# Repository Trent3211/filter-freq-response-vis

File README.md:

# Filter Frequency Response Visualizer
GitHub repo for SDSU Senior Design Team 18, Filter Frequency Response Visualizer, or FFRV

## SYSTEM DESCRIPTION

The FFRV system  will be a test box used for measuring the frequency response of a user-provided passive filter. Once started, the system will apply a frequency sweep across an inputted filter, then measure the filter output gain and phase shift using analog computations, inputted to an Arduino Due microcontroller. Thus, this FFRV system will calculate the Bode plots for a real-world filter. The purpose of the FFRV system is to allow students, hobbyists, and other casual filter-designers a rapid way to gain insight into simple filters, such as what frequencies they pass or reject. As such, the FFRV system will be designed to be straightforward to use. It shall have a box face with only a select few clearly-labeled inputs, and output a data file of the measurements to the user computer, connected over USB to the test box. The functional components in this system will include a procured waveform generator, a PCB for distributing power and performing analog analysis on filter magnitude and phase, an Arduino Due for converting the analog values to digital and controlling the waveform generator, and a NET application which will provide the user an interface to work with the system.

## USING GITHUB

### Basic Operation: 

Git is both local version control (local) and also cloud version control (remote). Version control is logging how changes are made to documents (think google docs history) so that way changes can be managed. This is useful in code, where you may have a working solution but you want to add features to it, so "committing" that version to a history log allows you to make changes, and always have a successful solution to return to. Basically, git is a way to log changes you make files, and then upload them to the cloud (have them stored virtually, rather than locally). That's the basic operation. There is more features that will be used, but at its most basic operation its changing files and then logging those changes. 

### Install Git:

__Create Git Repo Folder__
<br>
Purely for containment sakes, you may want to create a folder for holding all your GitHub repos. This is optional. If you already have a folder, then you have no need to create a new folder. I (Trent) would suggest creating a folder titled "GitHub-Repos" in your Documents folder on your computer. You can create that folder using the following CLI commands. (To open the terminal, type "Command Prompt" in the search function on your windows machine, then click on the application)
```
cd Documents
mkdir GitHub-Repos
cd GitHub-Repos
```
__Add the repository__
<br>
Go to the desired directory (if you followed the steps in "Create Git Repo Folder", you will already be in the desired folder) and clone the repository. The comand will look like the following
```
git clone https://github.com/Trent3211/filter-freq-response-vis.git <Optional: What you'd like the document to be named>
```
Sections wrapped by \< \> will want to be replaced by what is referred to in the section. You should be able to now see a folder with the title you provided in the `<Optional: ...>` section, or it will be titled filter-freq-reponse-vis. You can view this in your file explorer, or by using the `dir` command in the Terminal (Command Prompt). To verify that the repository was properly imported, open the folder using the Windows File explorer. Check the folder for the README.md file. Its contents should match this file. 

### Creating a commit: 

To use Git, you'll link your local to the remote. As you make changes to the whatever files you're editing (NET application, INO file, KiCAD schematic, LTSpice simulation, etc.) you'll want to mark good changes. You mark these changes with a "commit". Committing works in three phases. First, you add the files you want to a new commit (using command line interface arguments, or CLI). Second, you'll "commit" these changes to your local git with a message that describes the changes that we're made from the previous commit to the current commit (there is a standardized way for creating commit messages), using the CLI. Third, you will "push" your local changes to the remote, again using the CLI. The steps and their associated CLI arguments are shown below:
<br>

__0a) Go to repository:__ `cd <local file path for github repo> `
<br>
__0b) Pull any new changes:__ `git fetch`
<br>
__1) Add Files:__ `git add <file name1> <file name2> ... <file name x> `
<br>
-> NOTE: Use `git status` to see what changes you've made to files. Those that have been edited will appear in red. After you've added them, if you run `git status` again they should appear green.
<br>
__2) Create Log Message:__ `git commit `
<br>
-> NOTE: This will open the default text editor, "Vim". Vim slightly terrifies me, so I would recommend switching your default editor to Notepad. To set it to that text editor, see "Other Helpful CLI". See notes on creating an effective commit message in the section below
<br>
__3) Push Changes:__ `git push -u origin`
<br>
-> NOTE: origin refers to the cloud repository, as it is the first instantiation of the github repo. 
<br>
<br>
_Commit Message Best Practice_
<br>
There are two parts to a commit message: the subject header and a description. A subject header should encapsulate what was changed in the commit using 50 characters or less. If there is a lot more detail necessary to encapsulate the full picture, that's what the description is used for. Best practice for the subject header is to use the imperative tense. Examples include `Test new data`, or `Rewire ground and power planes`. A subject header should be formatted such that someone reading could read it as "If applied, this commit will ...", followed by the subject header. Thus, the following examples would read "This commit will: Test new data" or "This commit will: Rewire ground and power planes". 
<br>
After writing the subject header, two lines breaks will separate the subject header from the description. The description may add more detail not included in the subject header, reasoning for why the commit was needed, include details about testing and verification steps, or detail errors that were encountered with the version in the commit that will need to be fixed in future commits. Wrap each line of the description after 72 characters, otherwise it will be hard to read using the CLI. More detail on commit messages can be found here [https://gist.github.com/robertpainsi/b632364184e70900af4ab688decf6f53]. A good commit message may look like the following (the sections preceded by # are autogenerated by Git. They can be left in, they will not be included when viewing the message in the future):
```
Rewire ground and power planes

A previous commit had the ground and power planes connected to the same 
netlist. However, there are still some serious ratnests that may 
introduce noise. An issue has been added to the GitHub to address it.
# Please enter the commit message for your changes. Lines starting
# with '#' will be ignored, and an empty message aborts the commit.
#
# On branch fake-branch
# Your branch is up to date with 'origin/fake-branch'.
#
# Changes to be committed:
#       new file:   fake-file
```

### Creating and merging a branch

As we set up issues (think spots of development in achieving our long term milestones) in GitHub and try to solve them, we'll want to create new branches to address them. Branching keeps the main tree clean as solutions develop, so that they are only added into the `main` branch when they are finished being developed and have been reviewed by other members of the team. The naming convention for a branch is the issue number, followed by an underscore, and a 1 to 3 word description of what changes the branch encapsulates/will encapsulate. For example, a good name for a branch that addresses issue 0 of team members getting to know each other would be `0_starbucks_meeting`. Be sure to always branch from the main branch, rather than form other branches. This will keep the logging and version control easier to follow. The steps for creating a branch locally and publishing to the remote are shown below:
<br>
<br>
__0a) Update to the remote:__ 
<br>
Run `git fetch` to update your local repository with changes with those made in the remote (the online repository that we all access). Now run `git status` to see how many commits above or behind you are. If you have not made any changes that haven't yet been committed, run `git pull`. You will now be up-to-date with the remote and ready to proceed. 
<br>
__0b) Set to `main` branch:__ 
<br> Run `git status` using the CLI to make sure you are on the main branch. The first line of the text output should detail which branch you are on. If you are not on the main branch, run `git checkout main`. The output in this case should now be:
```
Switched to branch 'main'
Your branch is up to date with 'origin/main'.
```
__1) Create a new local branch:__ 
<br>
To create a new branch, there are two sets of commands you can choose. The first create a new branch off of the current branch, followed by a checkout command to switch to it. First run `git branch <Branch-Name>`. You can verify the branch was properly created by running `git branch`, which will list all available branches. Next, switch to the branch by running `git checkout <Branch-Name>`. The second method for creating a new branch both creates and switches to a branch in one command. This is `git checkout -b <Branch-Name>`. Only one of these two methods may be used to create and switch to a new branch--not both.
<br>
__2) Push branch to remote:__ 
<br>
In order to set up the branch so that it is remotely tracked, run `git push -u origin <Branch-Name>`. Now, when commits are made and pushed, they will be pushed to this branch in the remote. You are now free to add/change files and create commits
<br>
__3) Pull Request:__ 
<br>
The final part in a branches lifecycle is its death, which happens by merging it into the `main` branch. A merge into the `main` branch is called a pull request. It's poorly named, but there's no changing what GitHub refers to it as so so be it. You can find the list of branches on GitHub website by clicking "\<\> Code" when in the repositor folder. Click on the "Branches" tab. When you click on this, you will see a list of branches. Click on the "Pull Request" button next to the desired branch. Add a comment providing a paragraph description of what has been changed, and add reviewers for who should review the changes before its merged into `main`. Publish once you are ready.
<br>
### Other Helpful CLI:
`git checkout <branch name>`
<br>
`git branch`
Lists all branches currently visible on the local machine. (Other branches in the remote will be accessible using a `git checkout`, but may not be visible using git branch)
`git log` 
See all commits in the repository (if you've made new commits, these should show up here. It zhould also be synced with the remote if you've run `git fetch` and `git pull`)

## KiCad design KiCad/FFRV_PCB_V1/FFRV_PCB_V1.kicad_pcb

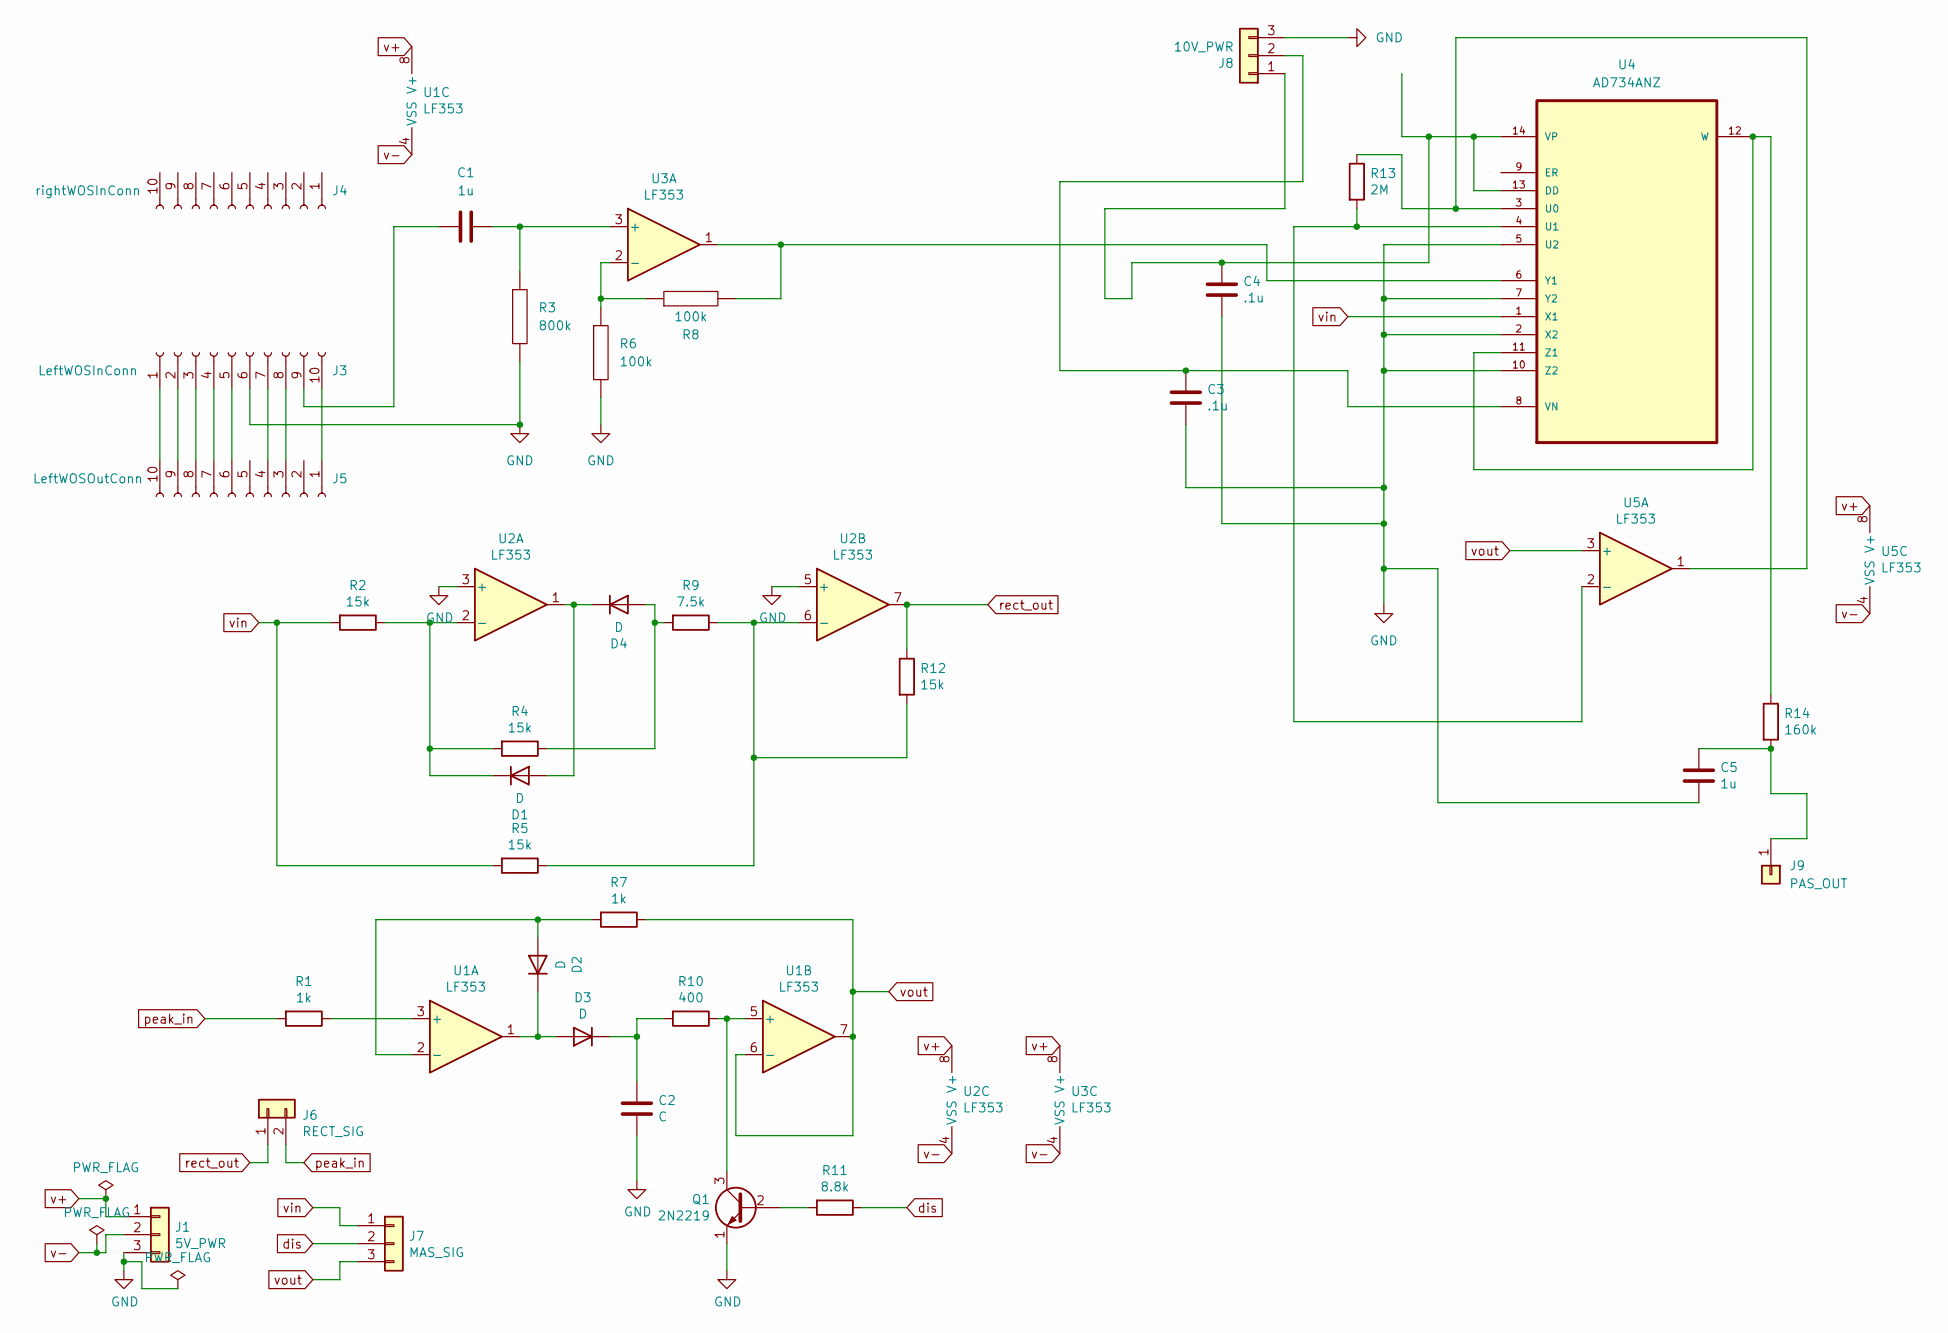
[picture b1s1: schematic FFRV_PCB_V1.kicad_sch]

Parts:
C1: 1u; C_Axial_L19.0mm_D7.5mm_P25.00mm_Horizontal
C2: C; C_Axial_L12.0mm_D6.5mm_P15.00mm_Horizontal
C3, C4: .1u; C_Disc_D3.0mm_W1.6mm_P2.50mm
C5: 1u; C_Axial_L22.0mm_D10.5mm_P27.50mm_Horizontal
D1, D2, D3, D4: D; R_Axial_DIN0207_L6.3mm_D2.5mm_P10.16mm_Horizontal
J1: 5V_PWR; PinSocket_1x03_P2.54mm_Vertical
J3: LeftWOSInConn; PinHeader_1x10_P2.54mm_Vertical
J4: rightWOSInConn; PinHeader_1x10_P2.54mm_Vertical
J5: LeftWOSOutConn; PinHeader_1x10_P2.54mm_Vertical
J6: RECT_SIG; PinSocket_1x02_P2.54mm_Vertical
J7: MAS_SIG; PinSocket_1x03_P2.54mm_Vertical
J8: 10V_PWR; PinSocket_1x03_P2.54mm_Vertical
J9: PAS_OUT; PinSocket_1x01_P2.54mm_Vertical
Q1: 2N2219; TO-39-3
R1, R7: 1k; R_Axial_DIN0207_L6.3mm_D2.5mm_P10.16mm_Horizontal
R2, R4, R5, R12: 15k; R_Axial_DIN0207_L6.3mm_D2.5mm_P10.16mm_Horizontal
R3: 800k; R_Axial_DIN0207_L6.3mm_D2.5mm_P10.16mm_Horizontal
R6, R8: 100k; R_Axial_DIN0207_L6.3mm_D2.5mm_P10.16mm_Horizontal
R9: 7.5k; R_Axial_DIN0207_L6.3mm_D2.5mm_P10.16mm_Horizontal
R10: 400; R_Axial_DIN0207_L6.3mm_D2.5mm_P10.16mm_Horizontal
R11: 8.8k; R_Axial_DIN0207_L6.3mm_D2.5mm_P10.16mm_Horizontal
R13: 2M; R_Axial_DIN0207_L6.3mm_D2.5mm_P10.16mm_Horizontal
R14: 160k; R_Axial_DIN0207_L6.3mm_D2.5mm_P10.16mm_Horizontal
U1, U2, U3, U5: LF353; DIP-8_W7.62mm
U4: AD734ANZ; DIP-14_W7.62mm; MPN AD734ANZ

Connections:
GND: C2.2, C3.2, C4.2, C5.2, J1.3, J3.6, J8.3, Q1.1 (E), R3.2, R6.2, U2.3 (+), U2.5 (+), U4.2 (X2), U4.5 (U2), U4.7 (Y2), U4.10 (Z2)
unnamed: C1.1, J3.9
unnamed: C1.2, R3.1, U3.3 (+)
unnamed: C2.1, D3.1 (K), R10.2
unnamed: C3.1, J8.2, U4.8 (VN)
unnamed: C4.1, J8.1, U4.13 (DD), U4.14 (VP)
unnamed: C5.1, J9.1, R14.2
unnamed: D1.1 (K), R2.1, R4.2, U2.2 (-)
unnamed: D1.2 (A), D4.1 (K), U2.1
unnamed: D2.1 (K), D3.2 (A), U1.1
unnamed: D2.2 (A), R7.2, U1.2 (-)
unnamed: D4.2 (A), R4.1, R9.2
unnamed: J3.1, J5.10
unnamed: J3.2, J5.9
unnamed: J3.3, J5.8
unnamed: J3.4, J5.7
unnamed: J3.5, J5.6
unnamed: J3.7, J5.4
unnamed: J3.8, J5.3
unnamed: J3.10, J5.1
unnamed: Q1.2 (B), R11.2
unnamed: Q1.3 (C), R10.1, U1.5 (+)
unnamed: R1.1, U1.3 (+)
unnamed: R6.1, R8.1, U3.2 (-)
unnamed: R8.2, U3.1, U4.6 (Y1)
unnamed: R5.1, R9.1, R12.2, U2.6 (-)
unnamed: R13.1, U4.3 (U0), U5.1
unnamed: R13.2, U4.4 (U1), U5.2 (-)
unnamed: R14.1, U4.11 (Z1), U4.12 (W)
dis: J7.2, R11.1
peak_in: J6.2, R1.2
rect_out: J6.1, R12.1, U2.7
v+: J1.1, U1.8 (V+), U2.8 (V+), U3.8 (V+), U5.8 (V+)
v-: J1.2, U1.4 (VSS), U2.4 (VSS), U3.4 (VSS), U5.4 (VSS)
vin: J7.1, R2.2, R5.2, U4.1 (X1)
vout: J7.3, R7.1, U1.6 (-), U1.7, U5.3 (+)

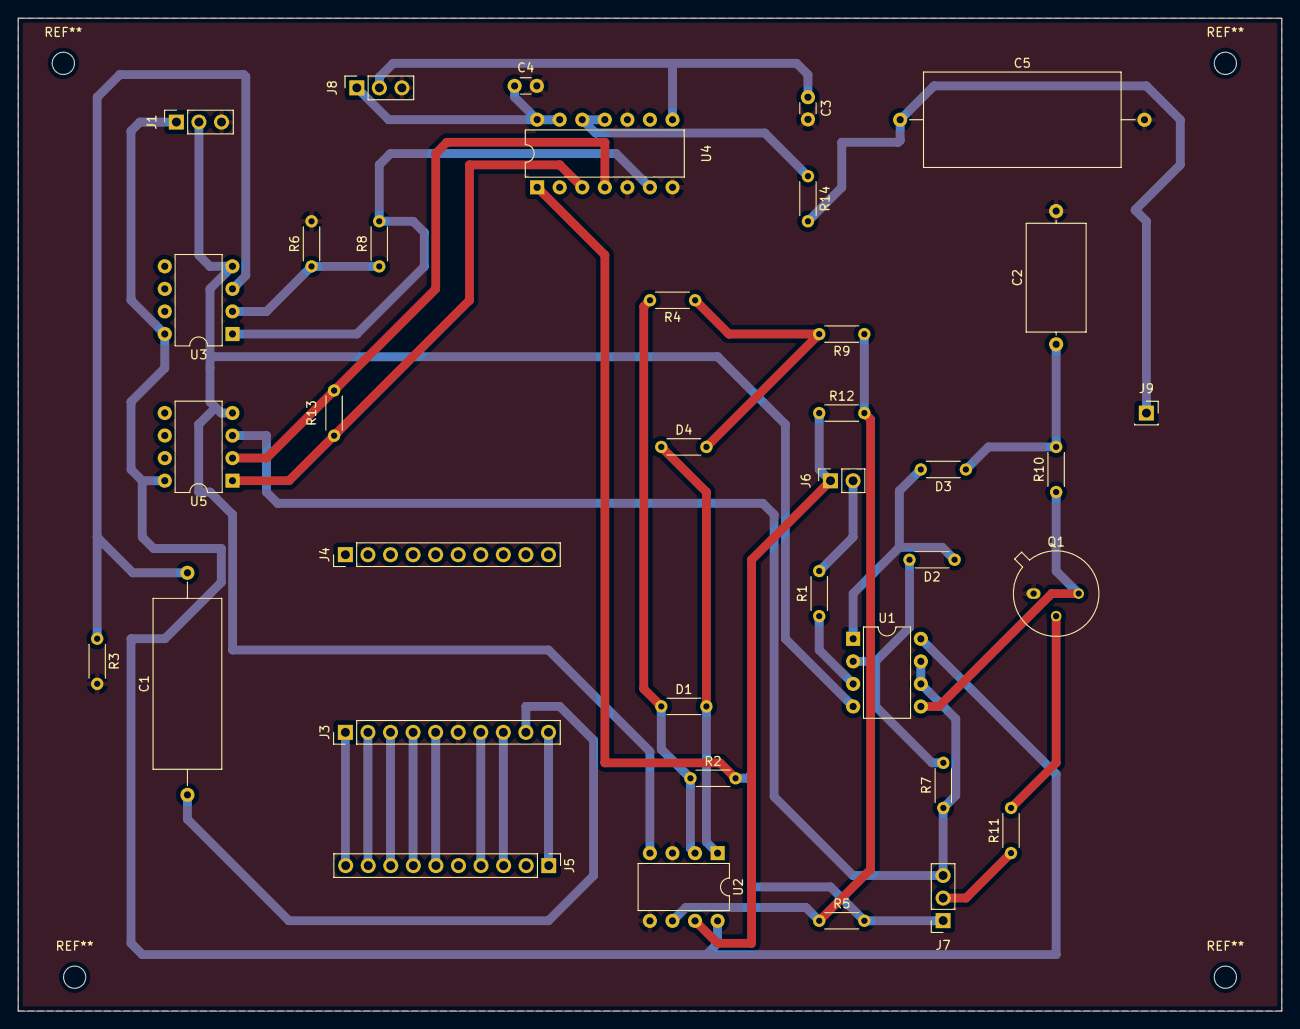
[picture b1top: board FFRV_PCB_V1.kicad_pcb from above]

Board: 2 copper layers, 142.2 x 111.8 mm, 37 parts (0 on the bottom side), 36 nets.

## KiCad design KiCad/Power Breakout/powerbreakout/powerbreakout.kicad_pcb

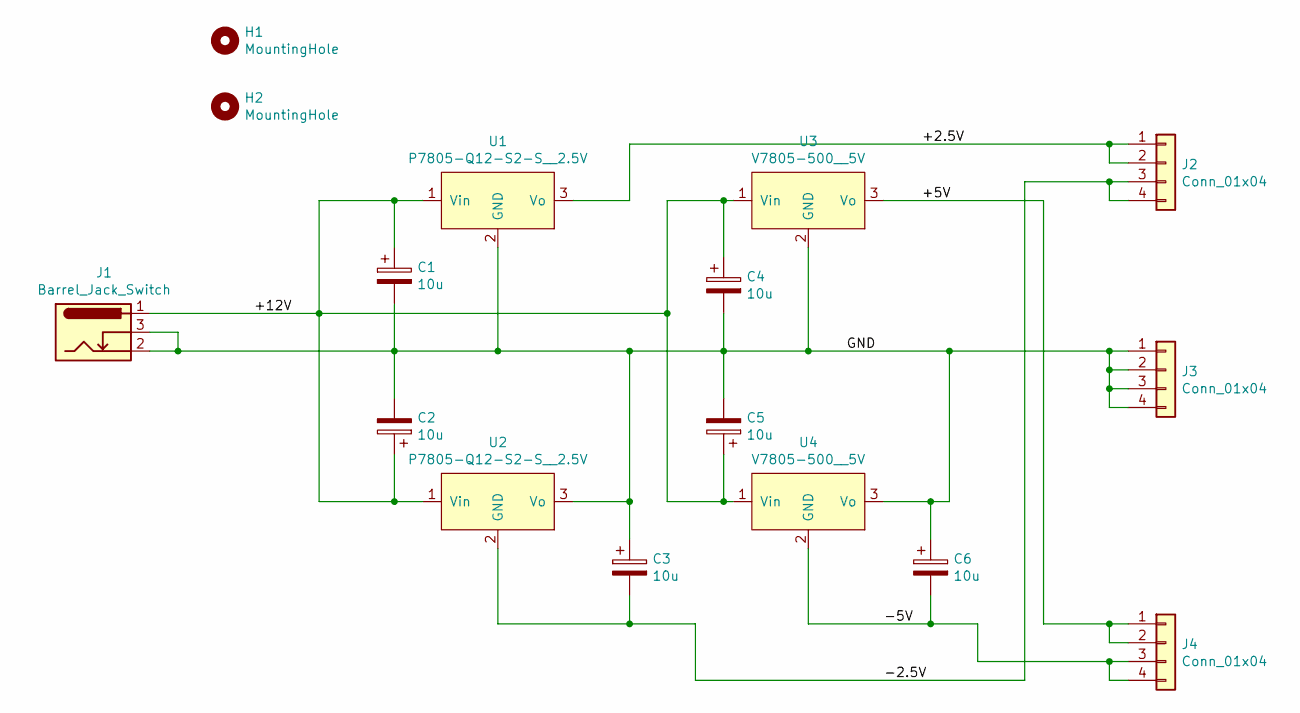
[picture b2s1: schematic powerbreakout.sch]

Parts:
C1, C2, C3, C4, C5, C6: 10u; C_Radial_D6.3mm_H7.0mm_P2.50mm
H1, H2: MountingHole; MountingHole_2.5mm
J1: Barrel_Jack_Switch; BarrelJack_Horizontal
J2, J3, J4: Conn_01x04; PinSocket_1x04_P2.54mm_Vertical
U1, U2: P7805-Q12-S2-S__2.5V; SIP3_11.6x8.5mm
U3, U4: V7805-500__5V; SIP3_11.6x8.5mm

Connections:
/+2.5V: J2.1, J2.2, U1.3 (Vo)
/+5V: J4.1, J4.2, U3.3 (Vo)
/+12V: C1.1, C2.1, C4.1, C5.1, J1.1, U1.1 (Vin), U2.1 (Vin), U3.1 (Vin), U4.1 (Vin)
/-2.5V: C3.2, J2.3, J2.4, U2.2 (GND)
/-5V: C6.2, J4.3, J4.4, U4.2 (GND)
/GND: C1.2, C2.2, C3.1, C4.2, C5.2, C6.1, J1.2, J1.3, J3.1, J3.2, J3.3, J3.4, U1.2 (GND), U2.3 (Vo), U3.2 (GND), U4.3 (Vo)

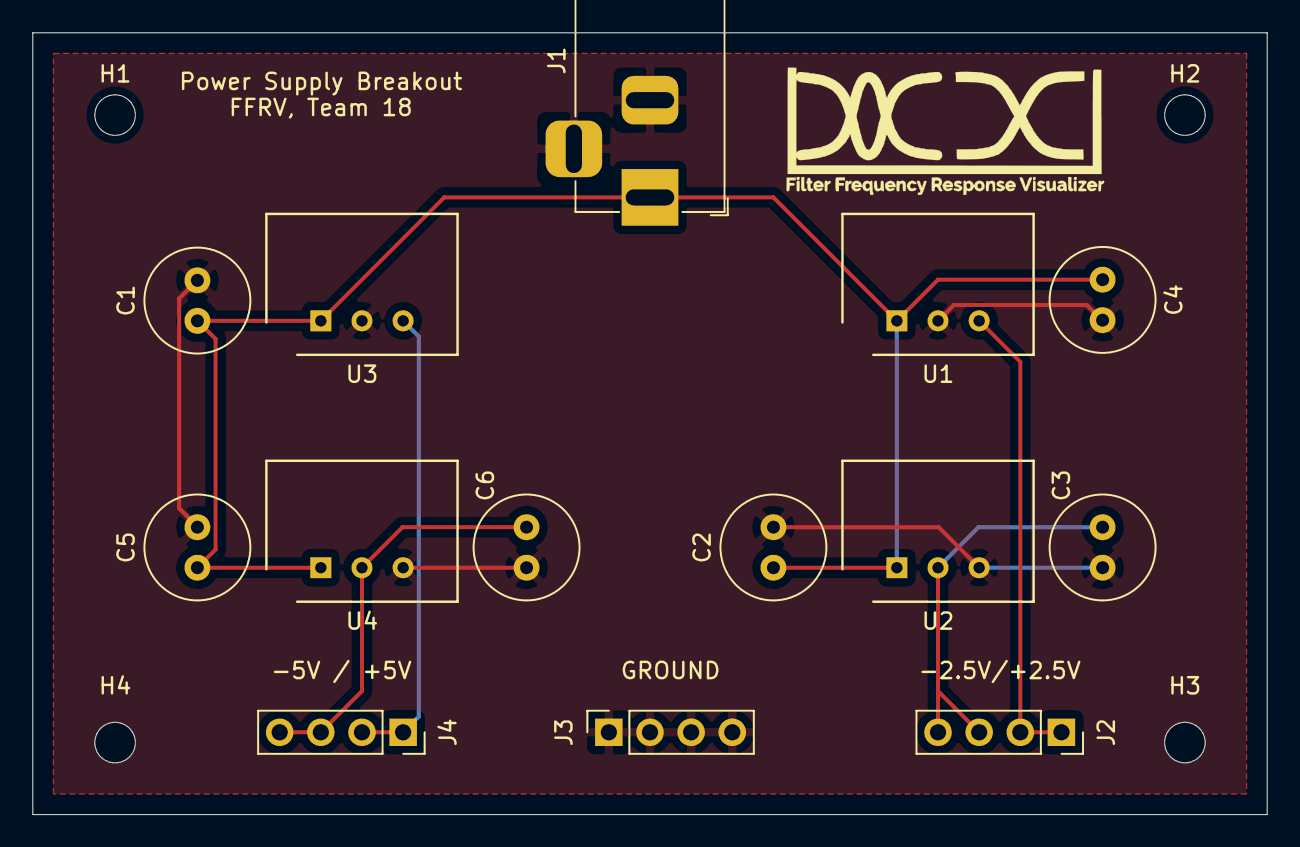
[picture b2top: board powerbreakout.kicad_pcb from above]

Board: 2 copper layers, 76.2 x 48.3 mm, 18 parts (0 on the bottom side), 6 nets.

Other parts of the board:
H3, H4: MountingHole; MountingHole_2.5mm

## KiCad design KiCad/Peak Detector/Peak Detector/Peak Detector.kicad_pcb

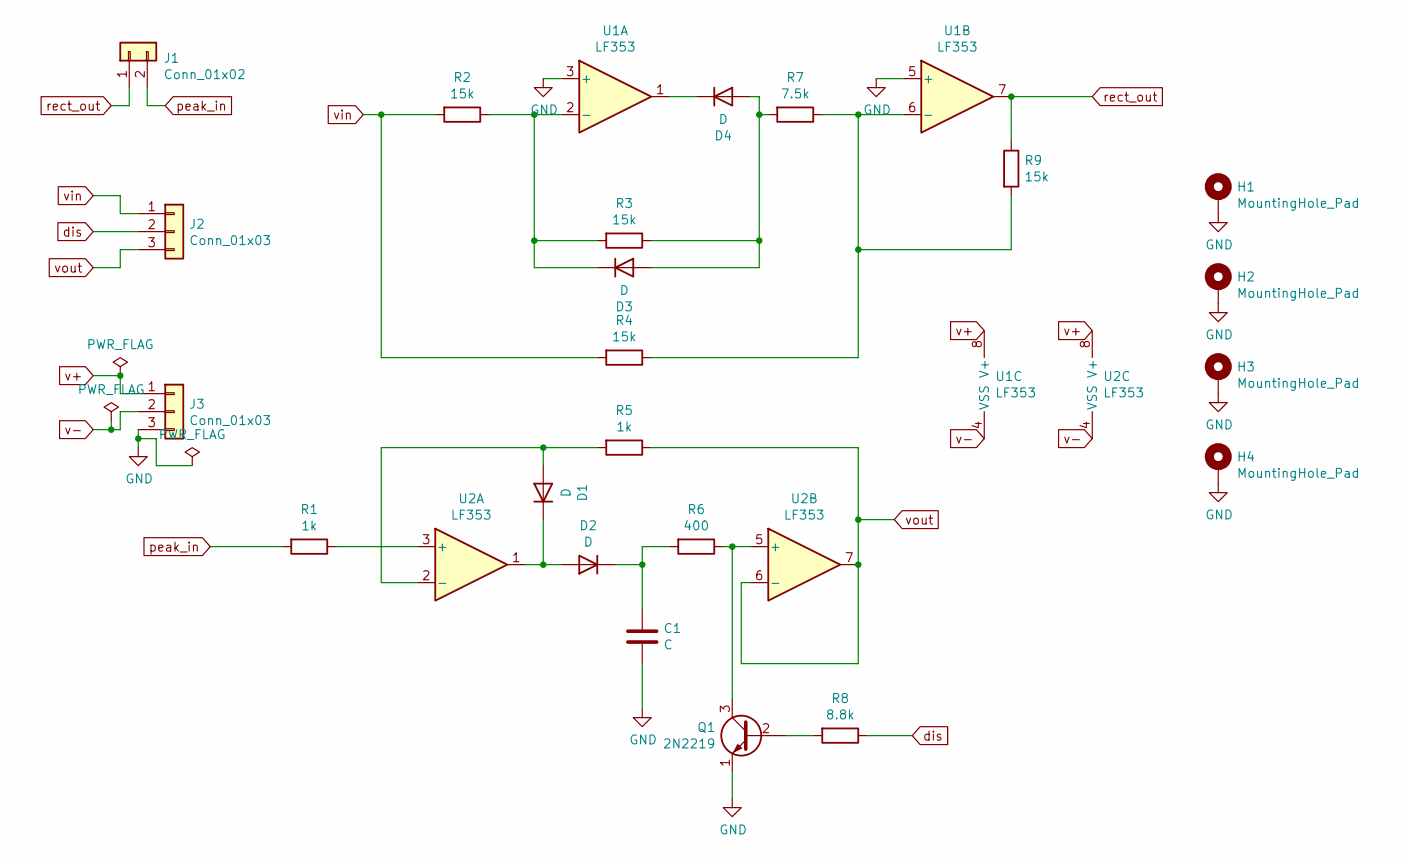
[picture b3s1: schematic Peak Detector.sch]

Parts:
C1: C; C_2225_5664Metric_Pad1.80x6.60mm_HandSolder
D1, D2, D3, D4: D; D_2512_6332Metric_Pad1.52x3.35mm_HandSolder
H1, H2, H3, H4: MountingHole_Pad; MountingHole_2.5mm
J1: Conn_01x02; PinSocket_1x02_P2.54mm_Vertical
J2, J3: Conn_01x03; PinSocket_1x03_P2.54mm_Vertical
Q1: 2N2219; TO-39-3
R1, R5: 1k; R_2512_6332Metric_Pad1.40x3.35mm_HandSolder
R2, R3, R4, R9: 15k; R_2512_6332Metric_Pad1.40x3.35mm_HandSolder
R6: 400; R_2512_6332Metric_Pad1.40x3.35mm_HandSolder
R7: 7.5k; R_2512_6332Metric_Pad1.40x3.35mm_HandSolder
R8: 8.8k; R_2512_6332Metric_Pad1.40x3.35mm_HandSolder
U1, U2: LF353; DIP-8_W7.62mm

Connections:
GND: C1.2, H1.1, H2.1, H3.1, H4.1, J3.3, Q1.1 (E), U1.3 (+), U1.5 (+)
unnamed: C1.1, D2.1 (K), R6.2
unnamed: D1.1 (K), D2.2 (A), U2.1
unnamed: D1.2 (A), R5.2, U2.2 (-)
unnamed: D3.1 (K), R2.1, R3.2, U1.2 (-)
unnamed: D3.2 (A), D4.2 (A), R3.1, R7.2
unnamed: D4.1 (K), U1.1
unnamed: Q1.2 (B), R8.2
unnamed: Q1.3 (C), R6.1, U2.5 (+)
unnamed: R1.1, U2.3 (+)
unnamed: R4.1, R7.1, R9.2, U1.6 (-)
dis: J2.2, R8.1
peak_in: J1.2, R1.2
rect_out: J1.1, R9.1, U1.7
v+: J3.1, U1.8 (V+), U2.8 (V+)
v-: J3.2, U1.4 (VSS), U2.4 (VSS)
vin: J2.1, R2.2, R4.2
vout: J2.3, R5.1, U2.6 (-), U2.7

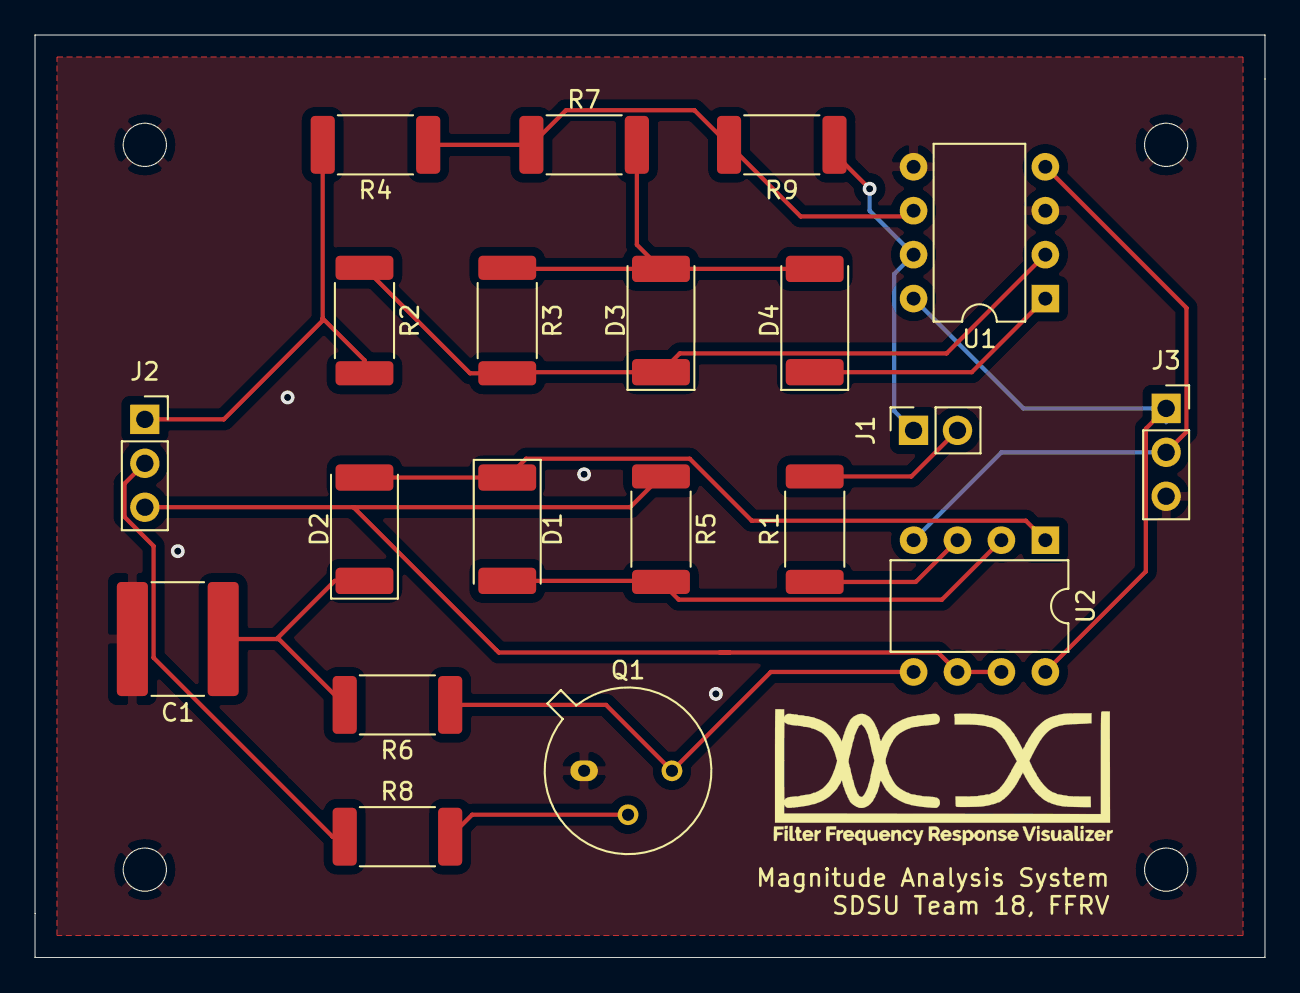
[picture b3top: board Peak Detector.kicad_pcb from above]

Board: 2 copper layers, 71.1 x 53.3 mm, 24 parts (0 on the bottom side), 18 nets.

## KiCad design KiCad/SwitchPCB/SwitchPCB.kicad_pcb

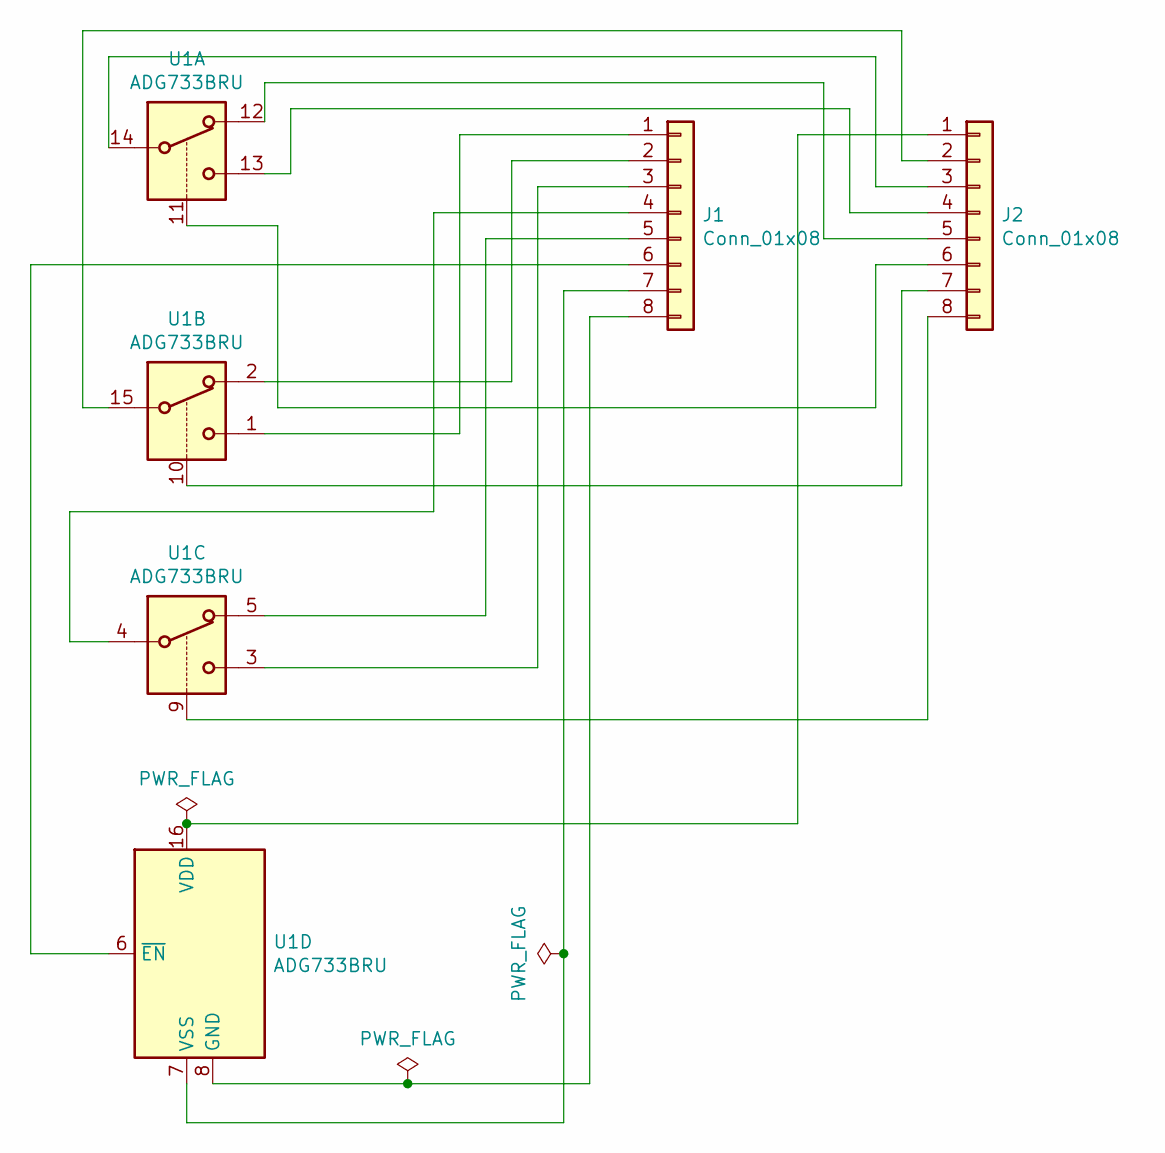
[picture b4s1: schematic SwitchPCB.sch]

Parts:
J1, J2: Conn_01x08; PinSocket_1x08_P2.54mm_Vertical
U1: ADG733BRU; TSSOP-16_4.4x5mm_P0.65mm

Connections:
unnamed: J1.1, U1.1
unnamed: J1.2, U1.2
unnamed: J1.3, U1.3
unnamed: J1.4, U1.4
unnamed: J1.5, U1.5
unnamed: J1.6, U1.6 (~EN)
unnamed: J1.7, U1.7 (VSS)
unnamed: J1.8, U1.8 (GND)
unnamed: J2.1, U1.16 (VDD)
unnamed: J2.2, U1.15
unnamed: J2.3, U1.14
unnamed: J2.4, U1.13
unnamed: J2.5, U1.12
unnamed: J2.6, U1.11
unnamed: J2.7, U1.10
unnamed: J2.8, U1.9

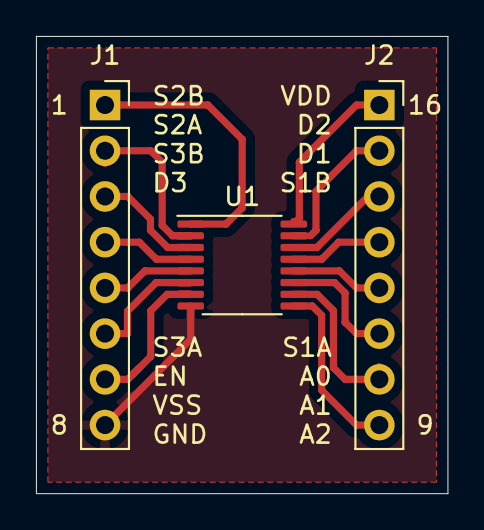
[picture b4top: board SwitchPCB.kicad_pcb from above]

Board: 2 copper layers, 22.9 x 25.4 mm, 3 parts (0 on the bottom side), 16 nets.

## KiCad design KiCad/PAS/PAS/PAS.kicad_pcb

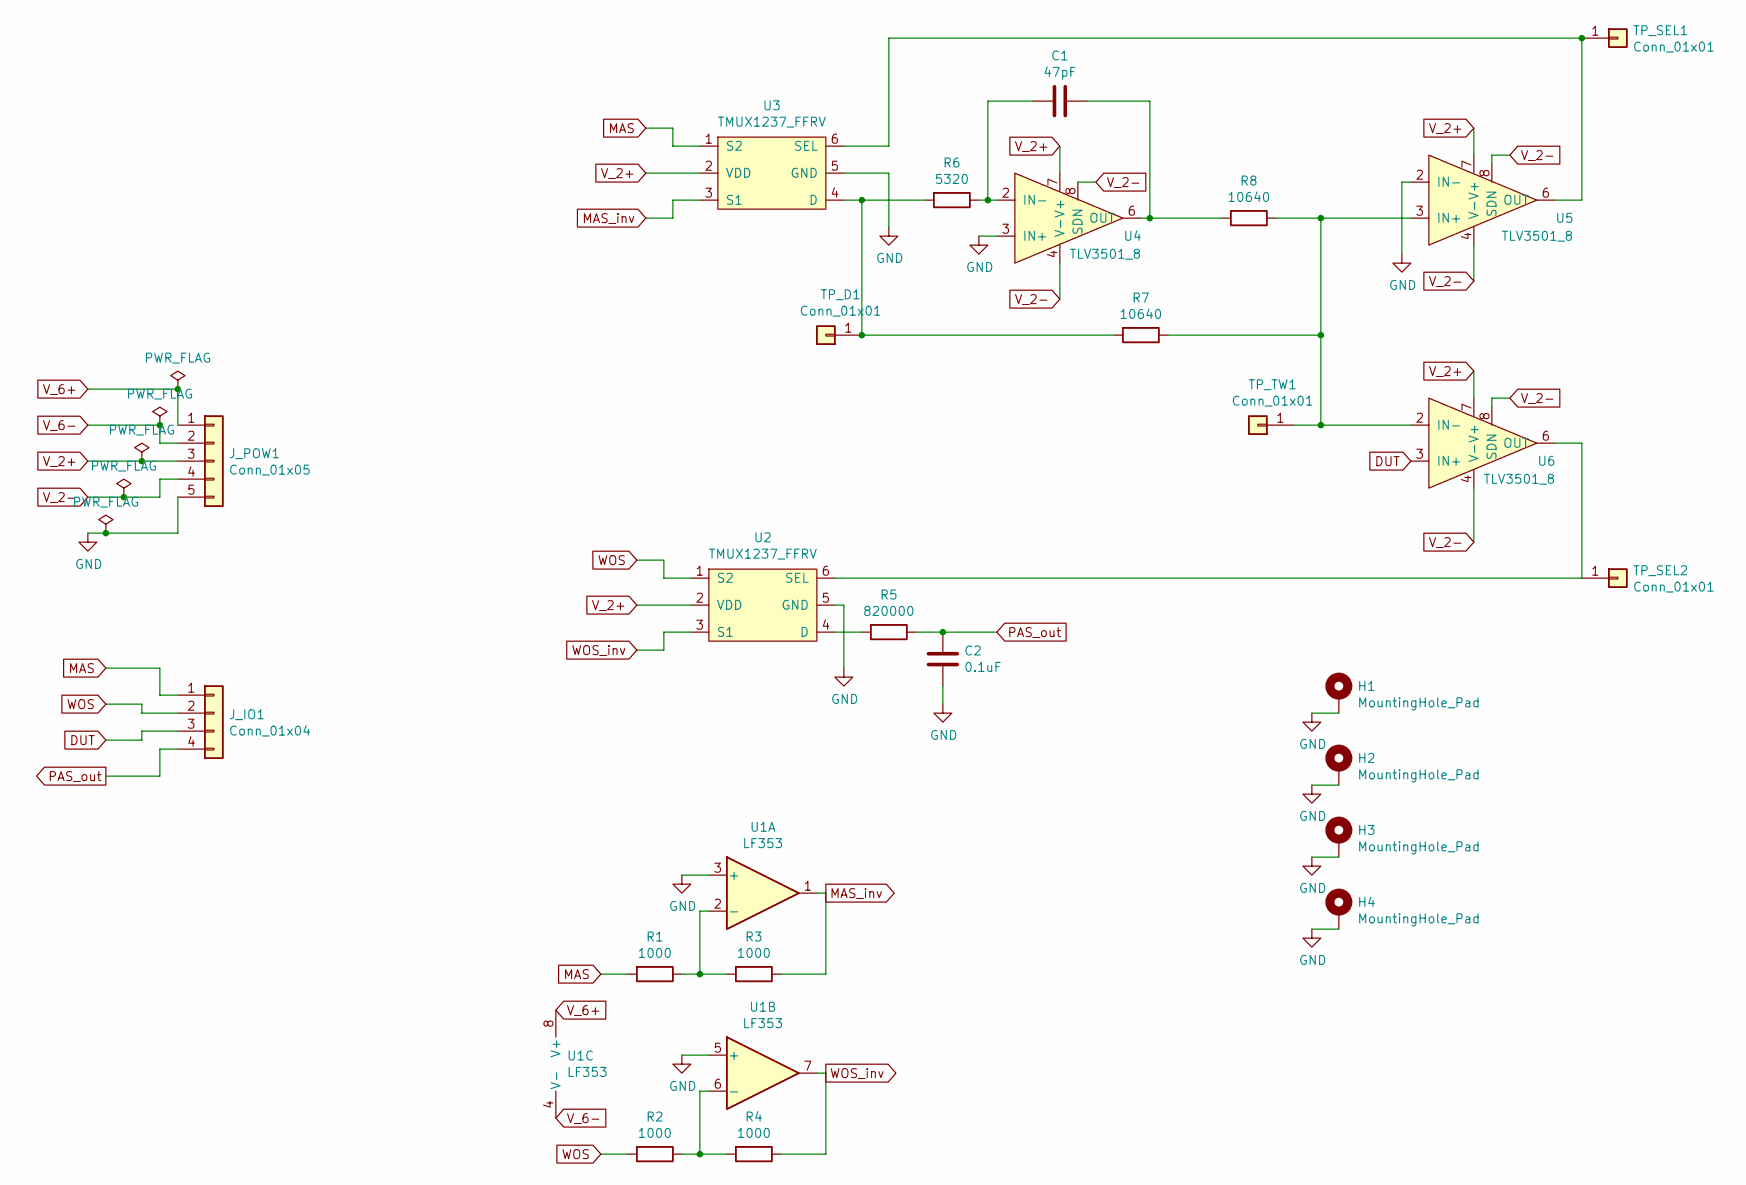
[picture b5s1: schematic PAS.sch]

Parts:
C1: 47pF; C_2225_5664Metric_Pad1.80x6.60mm_HandSolder
C2: 0.1uF; C_2225_5664Metric_Pad1.80x6.60mm_HandSolder
H1, H2, H3, H4: MountingHole_Pad; MountingHole_2.5mm_Pad
J_IO1: Conn_01x04; PinSocket_1x04_P2.54mm_Vertical
J_POW1: Conn_01x05; PinSocket_1x05_P2.54mm_Vertical
R1, R2, R3, R4: 1000; R_2512_6332Metric_Pad1.40x3.35mm_HandSolder
R5: 820000; R_2512_6332Metric_Pad1.40x3.35mm_HandSolder
R6: 5320; R_2512_6332Metric_Pad1.40x3.35mm_HandSolder
R7, R8: 10640; R_2512_6332Metric_Pad1.40x3.35mm_HandSolder
TP_D1: Conn_01x01; PinSocket_1x01_P2.54mm_Vertical
TP_SEL1, TP_SEL2: Conn_01x01; PinSocket_1x01_P2.54mm_Vertical
TP_TW1: Conn_01x01; PinSocket_1x01_P2.54mm_Vertical
U1: LF353; DIP-8_W7.62mm
U2, U3: TMUX1237_FFRV; SOT-23-6_Handsoldering
U4, U5, U6: TLV3501_8; SOIC-8_3.9x4.9mm_P1.27mm

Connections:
DUT: J_IO1.3, U6.3 (IN+)
GND: C2.2, H1.1, H2.1, H3.1, H4.1, J_POW1.5, U1.3 (+), U1.5 (+), U2.5 (GND), U3.5 (GND), U4.3 (IN+), U5.2 (IN-)
MAS: J_IO1.1, R1.2, U3.1 (S2)
MAS_inv: R3.1, U1.1, U3.3 (S1)
unnamed: C1.1, R8.2, U4.6 (OUT)
unnamed: C1.2, R6.1, U4.2 (IN-)
unnamed: R1.1, R3.2, U1.2 (-)
unnamed: R2.1, R4.2, U1.6 (-)
unnamed: R5.2, U2.4 (D)
unnamed: R6.2, R7.2, TP_D1.1, U3.4 (D)
unnamed: R7.1, R8.1, TP_TW1.1, U5.3 (IN+), U6.2 (IN-)
unnamed: TP_SEL1.1, U3.6 (SEL), U5.6 (OUT)
unnamed: TP_SEL2.1, U2.6 (SEL), U6.6 (OUT)
PAS_out: C2.1, J_IO1.4, R5.1
V_2+: J_POW1.3, U2.2 (VDD), U3.2 (VDD), U4.7 (V+), U5.7 (V+), U6.7 (V+)
V_2-: J_POW1.4, U4.4 (V-), U4.8 (SDN), U5.4 (V-), U5.8 (SDN), U6.4 (V-), U6.8 (SDN)
V_6+: J_POW1.1, U1.8 (V+)
V_6-: J_POW1.2, U1.4 (V-)
WOS: J_IO1.2, R2.2, U2.1 (S2)
WOS_inv: R4.1, U1.7, U2.3 (S1)

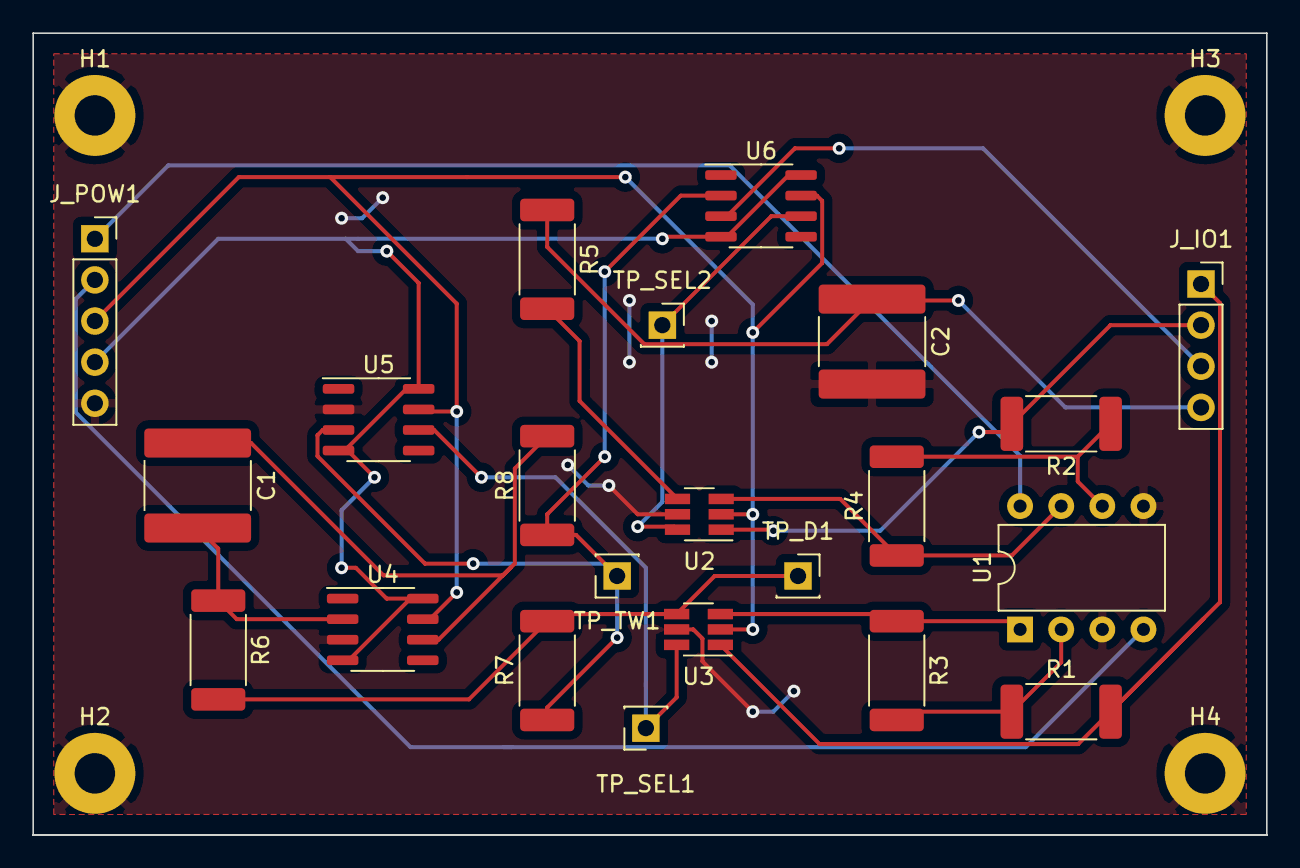
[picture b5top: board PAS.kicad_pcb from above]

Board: 2 copper layers, 76.2 x 49.5 mm, 26 parts (0 on the bottom side), 20 nets.
